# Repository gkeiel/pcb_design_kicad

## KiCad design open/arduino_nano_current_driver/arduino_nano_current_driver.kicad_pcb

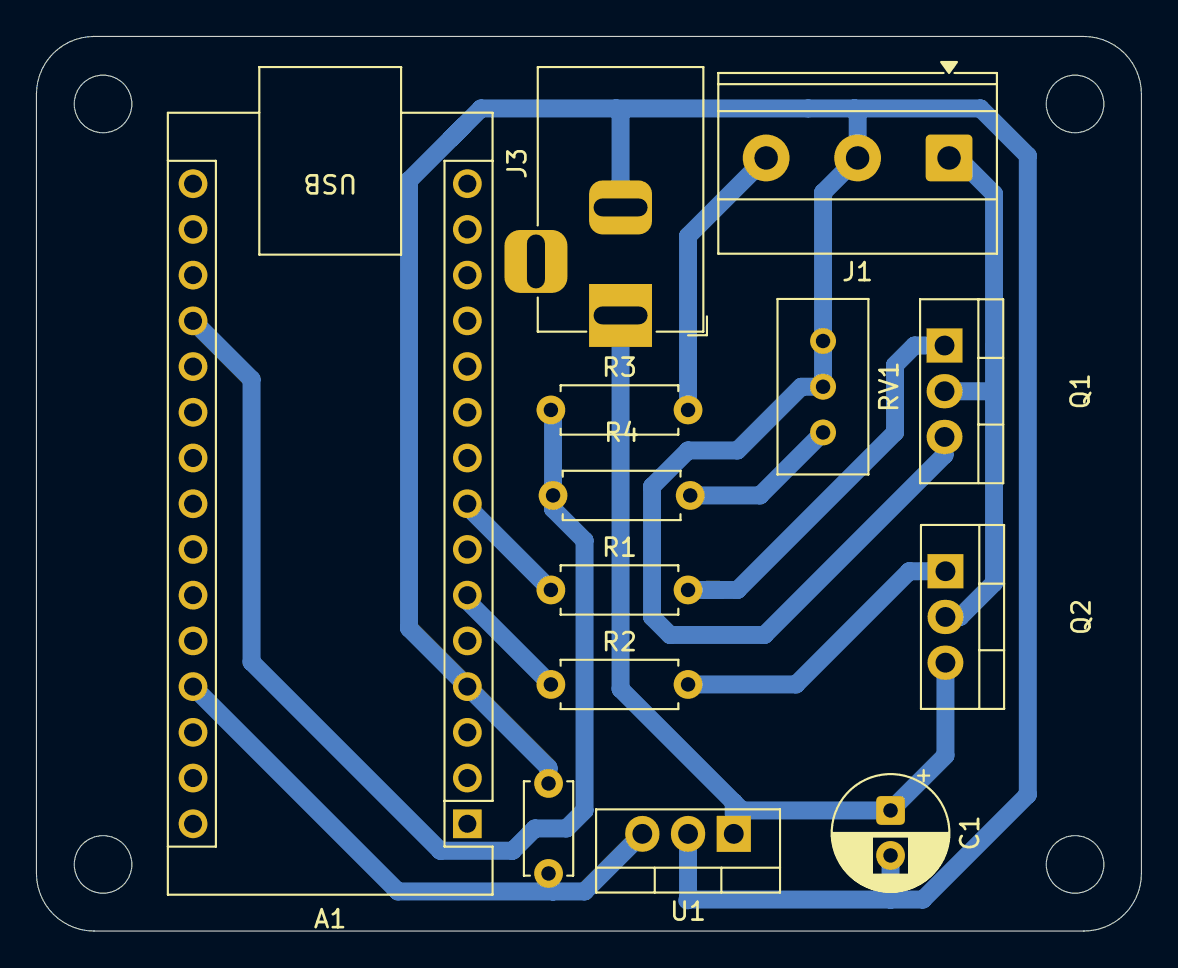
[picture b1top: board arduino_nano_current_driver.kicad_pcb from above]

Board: 2 copper layers, 61.4 x 49.7 mm, 13 parts (0 on the bottom side), 11 nets.

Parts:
A1: Arduino_Nano_v3.x; Arduino_Nano
C1: C_Polarized; CP_Radial_D6.3mm_P2.50mm
C2: C; C_Disc_D5.0mm_W2.5mm_P5.00mm
J1: Conn_01x03_Pin; TerminalBlock_Phoenix_MKDS-1,5-3-5.08_1x03_P5.08mm_Horizont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
J3: Barrel_Jack; BarrelJack_Horizontal
Q1: TIP41; TO-220-3_Vertical
Q2: TIP42; TO-220-3_Vertical
R1, R2, R3, R4: R; R_Axial_DIN0207_L6.3mm_D2.5mm_P7.62mm_Horizontal
RV1: R_Potentiometer_Trim_US; Potentiometer_Bourns_3296W_Vertical
U1: L7805; TO-220-3_Vertical

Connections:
A0: J1.3, R3.2
GND: A1.4 (GND), C1.2, C2.2, J1.2, J3.2, Q1.3 (E), RV1.2, RV1.3, U1.2 (GND)
unnamed: A1.27 (+5V), C2.1, U1.3 (OUT)
unnamed: A1.19 (A0), R3.1, R4.2
unnamed: A1.6 (D3), R2.1
unnamed: A1.8 (D5), R1.1
unnamed: J1.1, Q1.2 (C), Q2.2 (C)
unnamed: Q1.1 (B), R1.2
unnamed: Q2.1 (B), R2.2
unnamed: C1.1, J3.1, Q2.3 (E), U1.1 (IN)
unnamed: R4.1, RV1.1

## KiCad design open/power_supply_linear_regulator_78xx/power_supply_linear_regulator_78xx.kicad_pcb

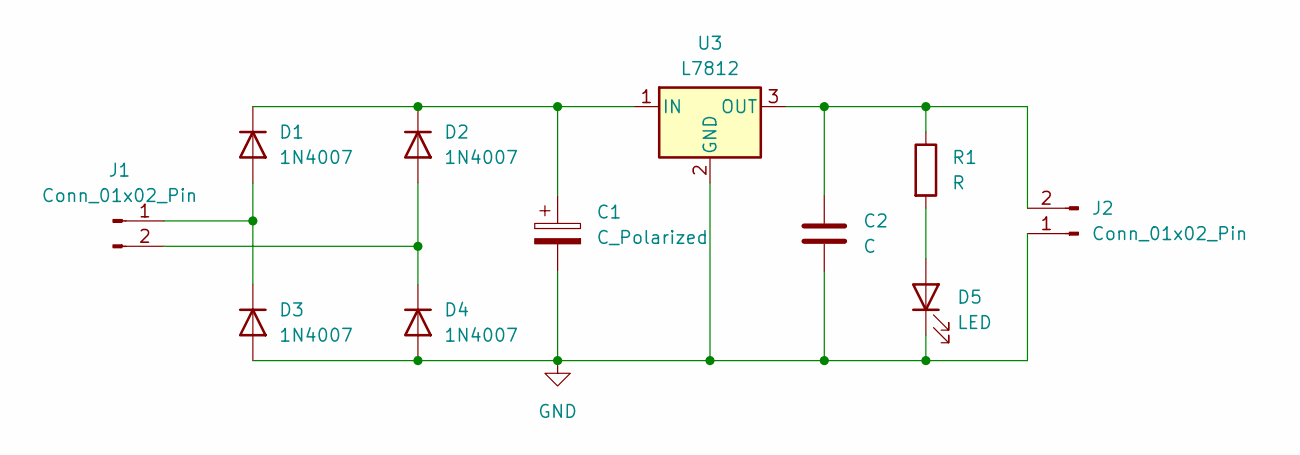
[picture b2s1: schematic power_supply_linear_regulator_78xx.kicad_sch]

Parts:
C1: C_Polarized; CP_Radial_D10.0mm_P5.00mm
C2: C; CP_Radial_D6.3mm_P2.50mm
D1, D2, D3, D4: 1N4007; D_DO-41_SOD81_P10.16mm_Horizontal
D5: LED; LED_D3.0mm
J1, J2: Conn_01x02_Pin; TerminalBlock_Phoenix_MKDS-1,5-2-5.08_1x02_P5.08mm_Horizont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
R1: R; R_Axial_DIN0207_L6.3mm_D2.5mm_P7.62mm_Horizontal
U3: L7812; TO-220-3_Vertical

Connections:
GND: C1.2, C2.2, D3.2 (A), D4.2 (A), D5.1 (K), J2.1, U3.2 (GND)
unnamed: D1.2 (A), D3.1 (K), J1.1
unnamed: C1.1, D1.1 (K), D2.1 (K), U3.1 (IN)
unnamed: D2.2 (A), D4.1 (K), J1.2
unnamed: D5.2 (A), R1.2
unnamed: C2.1, J2.2, R1.1, U3.3 (OUT)

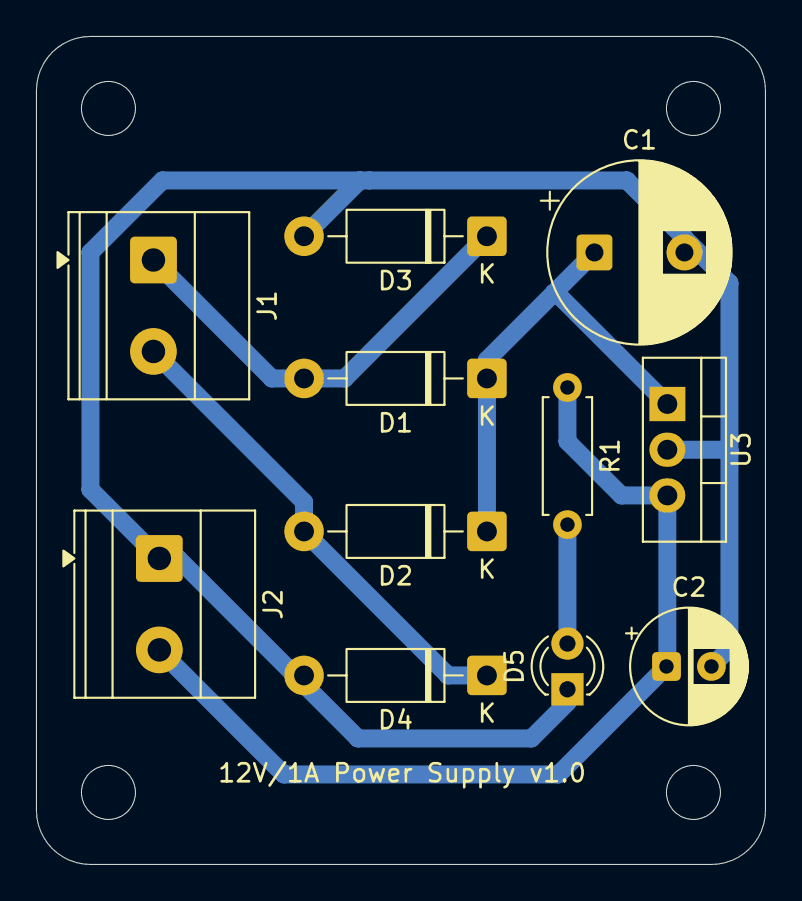
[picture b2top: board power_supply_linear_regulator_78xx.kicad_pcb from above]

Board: 2 copper layers, 40.5 x 46.0 mm, 11 parts (0 on the bottom side), 6 nets.

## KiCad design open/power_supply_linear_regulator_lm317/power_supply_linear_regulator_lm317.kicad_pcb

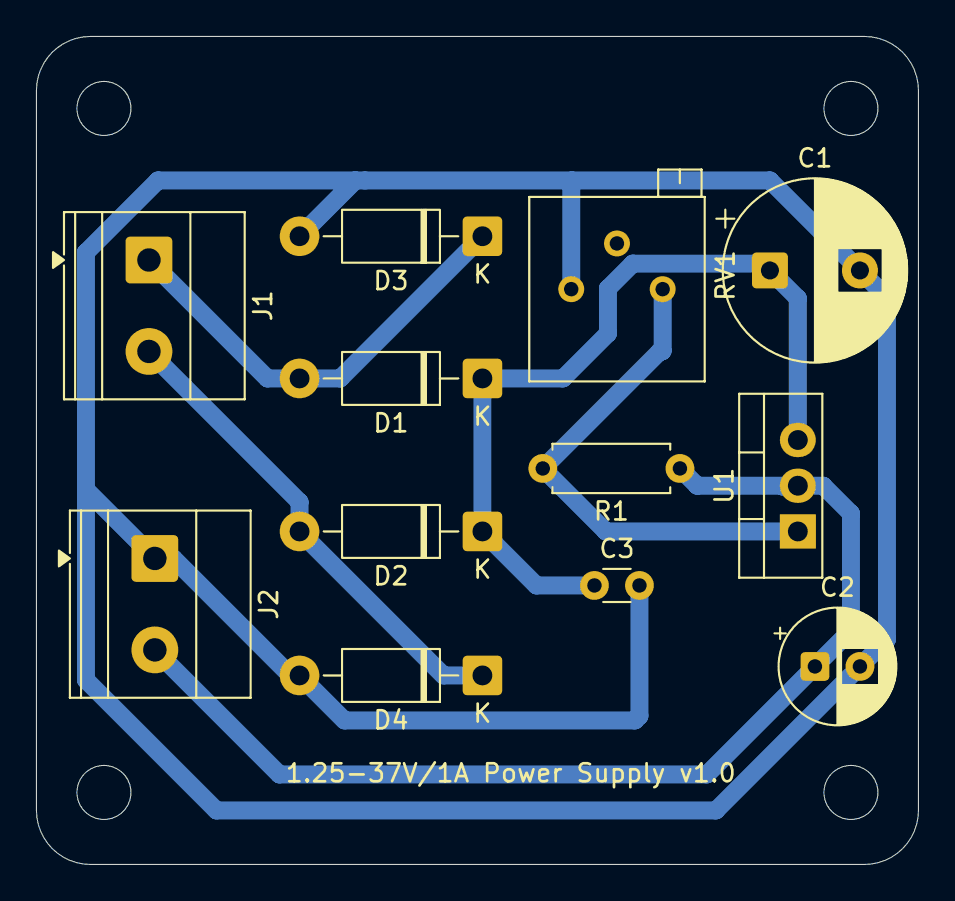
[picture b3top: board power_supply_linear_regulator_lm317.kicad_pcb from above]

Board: 2 copper layers, 49.0 x 46.0 mm, 12 parts (0 on the bottom side), 6 nets.

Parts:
C1: C_Polarized; CP_Radial_D10.0mm_P5.00mm
C2: C; CP_Radial_D6.3mm_P2.50mm
C3: C; C_Disc_D3.0mm_W1.6mm_P2.50mm
D1, D2, D3, D4: 1N4007; D_DO-41_SOD81_P10.16mm_Horizontal
J1, J2: Conn_01x02_Pin; TerminalBlock_Phoenix_MKDS-1,5-2-5.08_1x02_P5.08mm_Horizont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
R1: R; R_Axial_DIN0207_L6.3mm_D2.5mm_P7.62mm_Horizontal
RV1: R_Potentiometer_Trim_US; Potentiometer_Bourns_3296P_Horizontal
U1: LM317_TO-220; TO-220-3_Vertical

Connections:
GND: C1.2, C2.2, C3.2, D3.2 (A), D4.2 (A), J2.1, RV1.3
unnamed: D1.2 (A), D3.1 (K), J1.1
unnamed: C1.1, C3.1, D1.1 (K), D2.1 (K), U1.3 (VI)
unnamed: D2.2 (A), D4.1 (K), J1.2
unnamed: C2.1, J2.2, R1.1, U1.2 (VO)
unnamed: R1.2, RV1.1, U1.1 (ADJ)

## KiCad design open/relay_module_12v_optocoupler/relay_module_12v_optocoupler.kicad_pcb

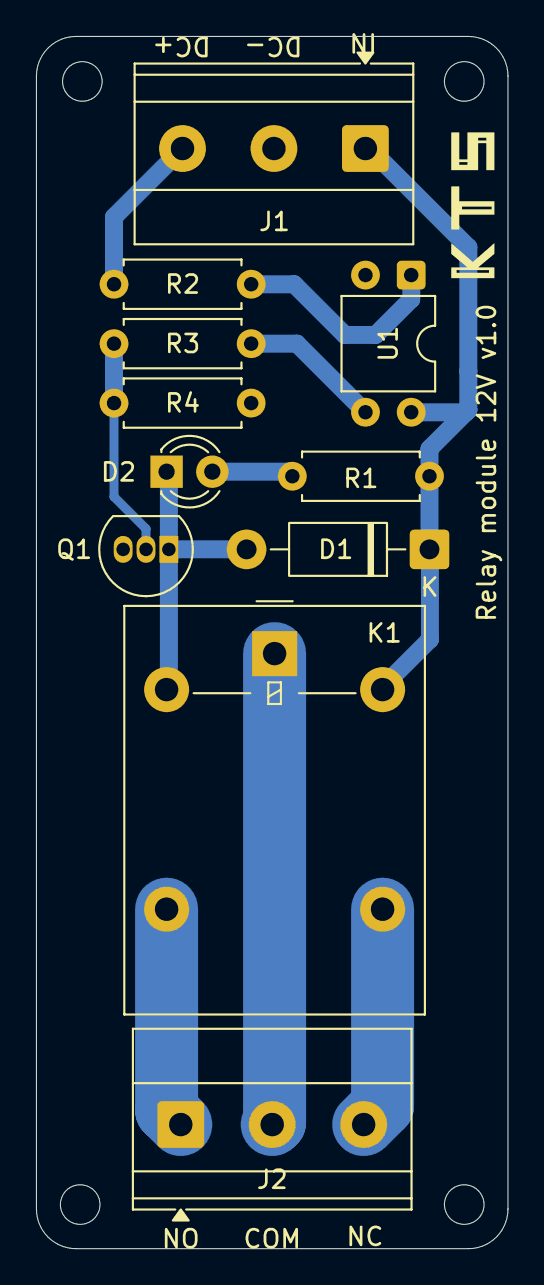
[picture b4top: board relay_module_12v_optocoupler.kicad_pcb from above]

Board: 2 copper layers, 26.2 x 67.3 mm, 11 parts (0 on the bottom side), 11 nets.

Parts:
D1: 1N4007; D_DO-41_SOD81_P10.16mm_Horizontal
D2: LED; LED_D3.0mm
J1: Conn_01x02_Pin; TerminalBlock_Phoenix_MKDS-1,5-3-5.08_1x03_P5.08mm_Horizont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
J2: Conn_01x03_Pin; TerminalBlock_Phoenix_MKDS-1,5-3-5.08_1x03_P5.08mm_Horizont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
K1: Relay_SPDT; Relay_SPDT_Omron-G5LE-1
Q1: BC337; TO-92_Inline
R1, R2, R3, R4: R; R_Axial_DIN0207_L6.3mm_D2.5mm_P7.62mm_Horizontal
U1: PC817; DIP-4_W7.62mm

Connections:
C_1: J2.2, K1.3
GND: J1.2, Q1.3 (E), R4.1, U1.2
NC_1: J2.3, K1.4
NO_1: J2.1, K1.5
unnamed: D1.2 (A), D2.1 (K), K1.2, Q1.1 (C)
unnamed: D1.1 (K), J1.1, K1.1, R1.1, U1.4
unnamed: D2.2 (A), R1.2
unnamed: J1.3, R2.1
unnamed: Q1.2 (B), R3.2, R4.2
unnamed: R2.2, U1.1
unnamed: R3.1, U1.3

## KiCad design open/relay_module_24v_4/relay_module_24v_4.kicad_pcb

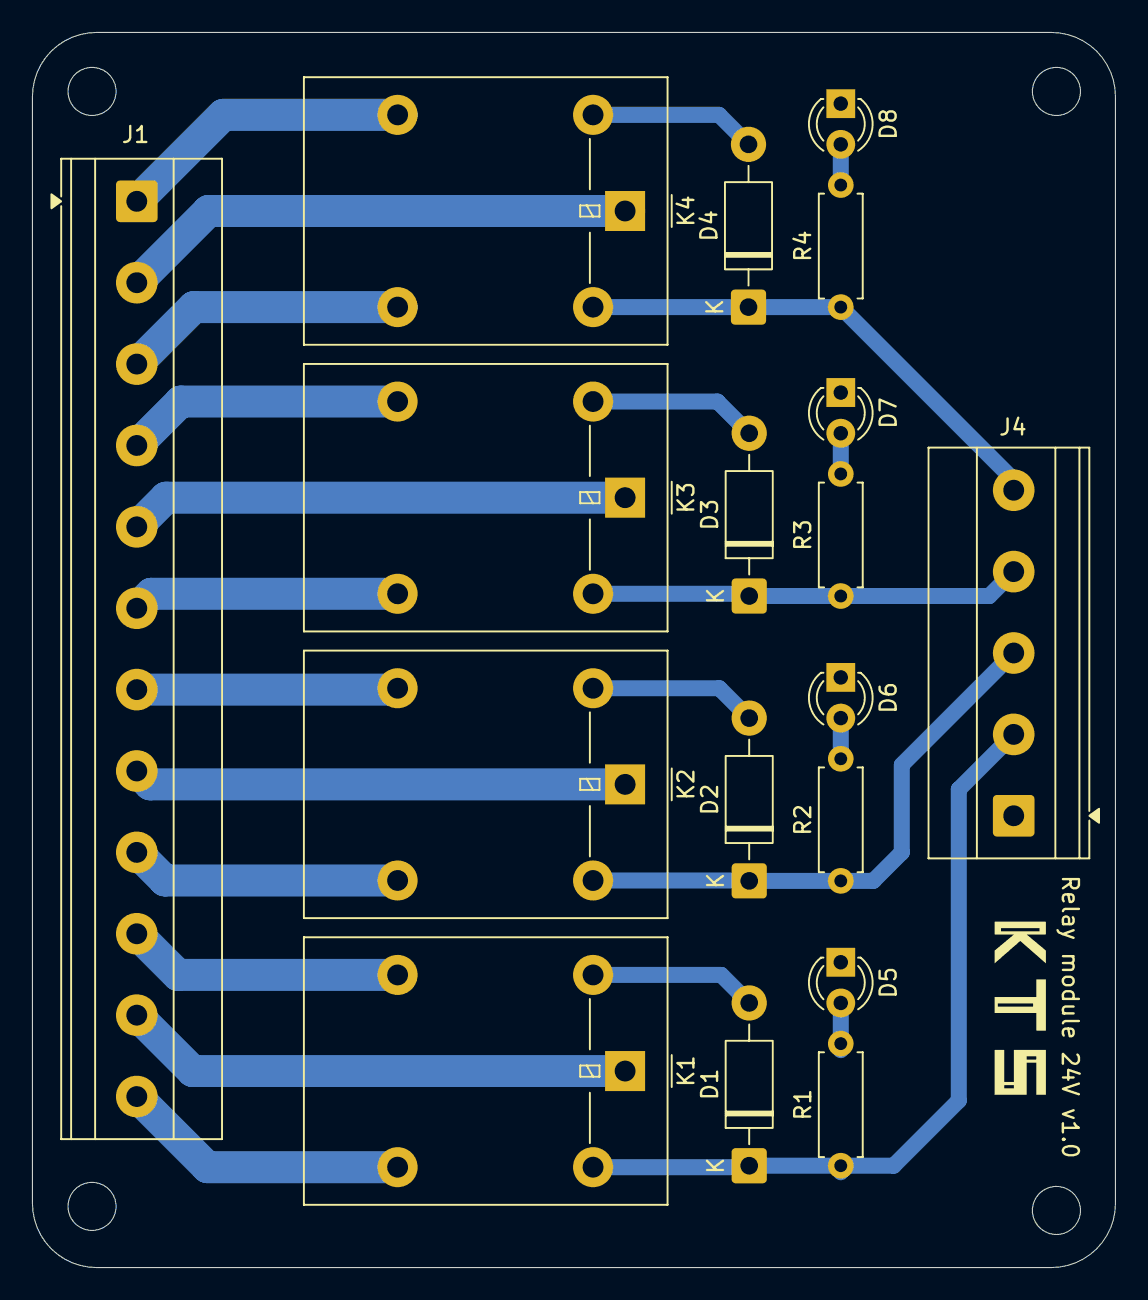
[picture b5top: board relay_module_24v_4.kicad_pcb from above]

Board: 2 copper layers, 67.6 x 77.1 mm, 18 parts (0 on the bottom side), 21 nets.

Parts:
D1, D2, D3, D4: 1N4007; D_DO-41_SOD81_P10.16mm_Horizontal
D5, D6, D7, D8: LED; LED_D3.0mm
J1: Conn_01x12_Pin; TerminalBlock_Phoenix_MKDS-1,5-12-5.08_1x12_P5.08mm_Horizon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
J4: Conn_01x05_Pin; TerminalBlock_Phoenix_MKDS-1,5-5-5.08_1x05_P5.08mm_Horizont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
K1, K2, K3, K4: Relay_SPDT; Relay_SPDT_Omron-G5LE-1
R1, R2, R3, R4: R; R_Axial_DIN0207_L6.3mm_D2.5mm_P7.62mm_Horizontal

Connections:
C_1: J1.11, K1.3
C_2: J1.8, K2.3
C_3: J1.5, K3.3
C_4: J1.2, K4.3
GND: D1.2 (A), D2.2 (A), D3.2 (A), D4.2 (A), D5.1 (K), D6.1 (K), D7.1 (K), D8.1 (K), J4.1, K1.2, K2.2, K3.2, K4.2
NC_1: J1.12, K1.4
NC_2: J1.9, K2.4
NC_3: J1.6, K3.4
NC_4: J1.3, K4.4
NO_1: J1.10, K1.5
NO_2: J1.7, K2.5
NO_3: J1.4, K3.5
NO_4: J1.1, K4.5
unnamed: D1.1 (K), J4.2, K1.1, R1.1
unnamed: D2.1 (K), J4.3, K2.1, R2.1
unnamed: D3.1 (K), J4.4, K3.1, R3.1
unnamed: D4.1 (K), J4.5, K4.1, R4.1
unnamed: D5.2 (A), R1.2
unnamed: D6.2 (A), R2.2
unnamed: D7.2 (A), R3.2
unnamed: D8.2 (A), R4.2
